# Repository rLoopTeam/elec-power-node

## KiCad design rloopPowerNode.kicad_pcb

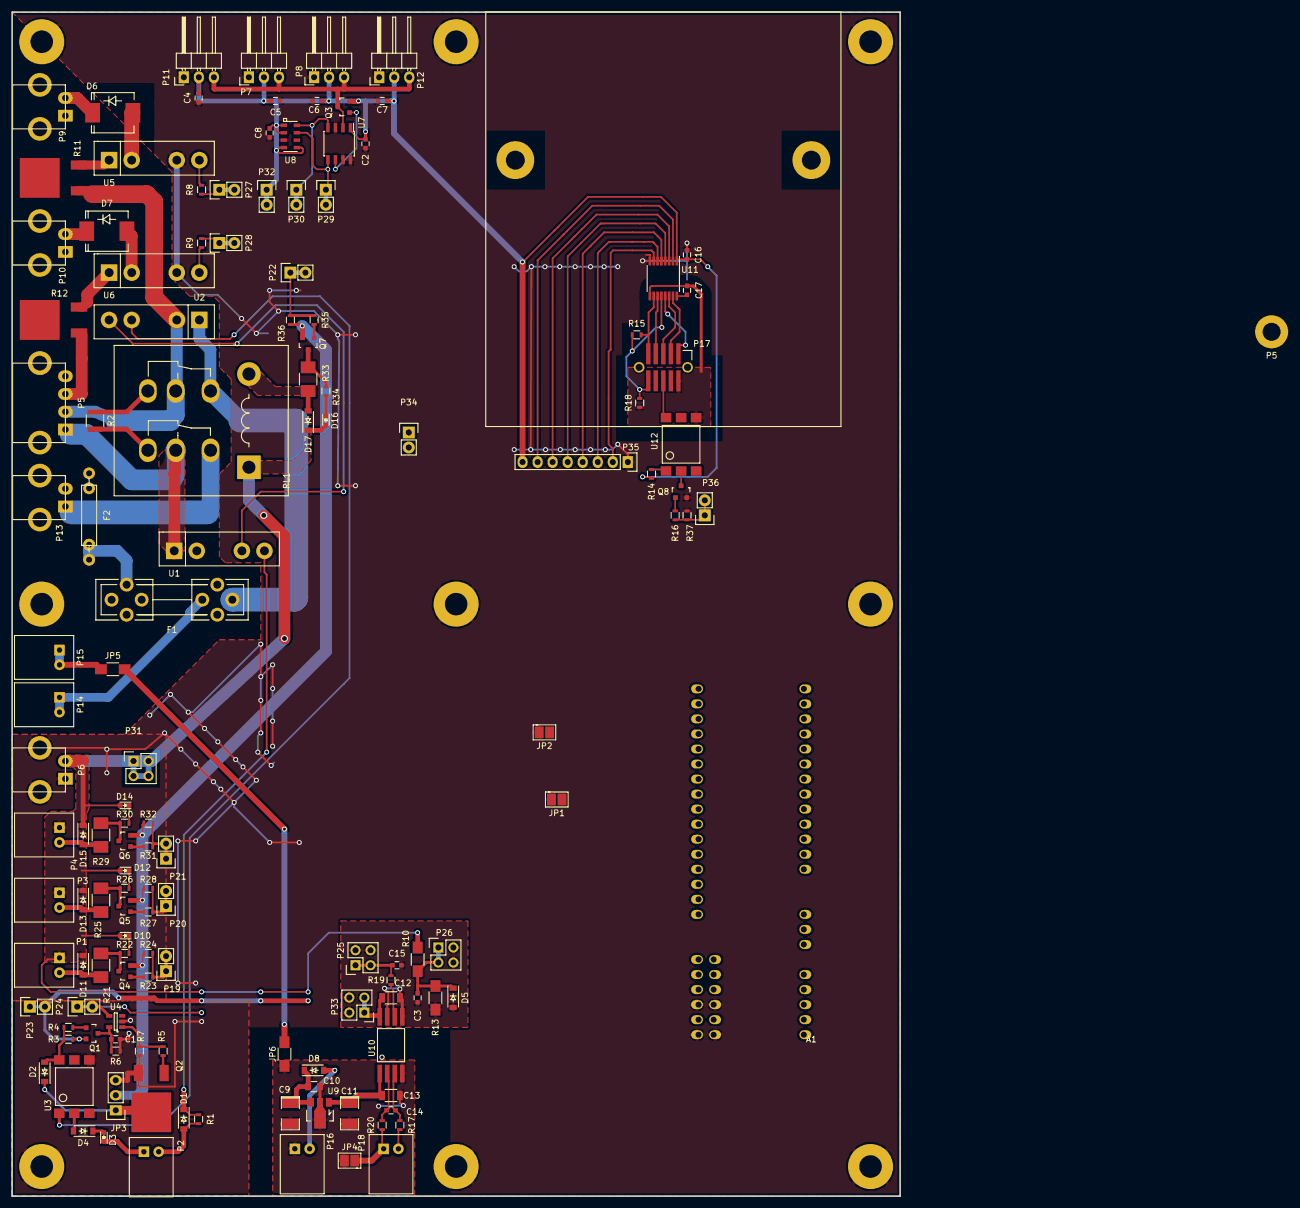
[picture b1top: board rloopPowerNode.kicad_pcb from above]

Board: 4 copper layers, 150.0 x 200.0 mm, 138 parts (0 on the bottom side), 96 nets.

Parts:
A1: NODE_CORE_CONNECTOR; NODE-CORE
C1, C2, C3, C8, C14, C16, C17: 100n; C_0603
C4, C5, C6, C7, C15: 1u; C_0603
C9, C11: 4u7; SMD-1210_Pol
C10: 1u; C_0805
C12, C13: 100n; C_1206
D1, D4, D8, D11, D13, D15, D17: D; SOD-123
D2: D_Schottky; SOD-123
D3, D10, D12, D14, D16: LED; LED_0603
D5: ZENER +2V7; SOD-123
D6, D7: D; SMC_Standard
F1: FUSE; Fuseholder5x20_horiz_open_universal_Type-III
F2: FUSE; FUSE-MULTICHOICE
JP1, JP2, JP4: Jumper_NC_Small; SOLDERJUMPER
JP3: JUMPER3; Pin_Header_Straight_1x03
JP5, JP6: Jumper_NC_Small; R_1206_HandSoldering
P1, P2, P3, P4, P14, P15, P16: CONN_01X02; CONN-JST-XH-2-PTH-RGT
P5: CONN_01X04; CONN-TE-MICROMNL-4-PTH-MALE-RGT
P5#2: CONN_01X01; SCREWPAD-4-40
P6, P9, P10, P13: CONN_01X02; CONN-TE-MICROMNL-2-PTH-MALE-RGT
P7, P8, P11, P12: CONN_01X03; Pin_Header_Angled_1x03
P17: AMPMODU-02X05; BMS
P18: SHUNT; CONN-JST-XH-2-PTH-RGT
P19, P20, P21, P22, P23, P24, P27, P28, P29, P30, P32, P34, P36: CONN_01X02; Pin_Header_Straight_1x02
P25, P26, P31, P33: CONN_02X02; Pin_Header_Straight_2x02
P35: CONN_01X08; Pin_Header_Straight_1x08
PCB1: PCB-OUTLINE; PCBOUTLINE-POWERNODE
Q1: PMOS; SOT-23
Q2: NMOS; D-Pak_TO252AA
Q3: BSS84; SOT-23
Q4, Q5, Q6, Q7: NMOS; SOT-23
Q8: Q_NMOS; SOT-23
R1: ?; R_0603
R2: 1K; R_1210
R3, R7, R15, R18, R24, R28, R32, R36, R37: 100K; R_0603
R4, R5, R14, R16: 470; R_0603
R6: 10K; R_0603
R8, R9, R19: 100; R_0603
R10: 100K; R_1206_HandSoldering
R11: 100; D-Pak-TO252AA-Resistor
R12: 10; D-Pak-TO252AA-Resistor
R13: 10K; R_1206_HandSoldering
R17, R20: 10; R_0603
R21, R25, R29, R33: R; R_1210_HandSoldering
R22, R26, R30, R34: 2K; R_0603
R23, R27, R31, R35: 470R; R_0603
RL1: Relay_DPDT; RELAY-SOCKET-K10
U1, U2, U5, U6: CPC1718
U3, U12: H11F1SM; OPTOCOUPLER-0.1in-6pin-SMD
U4: MAX6814; SOT-23-5
U7: DS2482-100; SOIC-8_3.9x4.9mm_Pitch1.27mm
U8: MS5607-02BA03; MS56xx
U9: 78L05; SOT89-3-VREG
U10: AMC1100; SOIC-8-W
U11: MAX14850; TSSOP-16_4.4x5mm_Pitch0.65mm

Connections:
+3.3V: P32.1, P32.2, P33.1, P33.3
+3V3: A1.+3V3, C2.2, C4.2, C5.2, C6.2, C7.2, C8.2, C12.1, C16.2, P7.2, P8.2, P11.2, P12.2, P35.8, Q3.2, R14.2, U7.1, U8.1, U8.2, U8.4, U8.5, U10.8, U11.1
+5V: A1.+5V, P23.1, P23.2, Q1.2, R3.1
+5V-HV: C11.1, C13.2, U9.VO, U10.1
+24V: D10.2, D11.1, D12.2, D13.1, D14.2, D15.1, D16.2, D17.1, P1.1, P3.1, P4.1, P6.2, P31.1, P31.2, P31.3, P31.4, P34.1, P34.2, R10.1, RL1.1
/Relay Driver 1/RELAY-NEG: D11.2, P1.2, R21.1
/Relay Driver 2/RELAY-NEG: D13.2, P3.2, R25.1
/Relay Driver 3/RELAY-NEG: D15.2, P4.2, R29.1
/Relay Driver 4/RELAY-NEG: D17.2, R33.1, RL1.2
BATT-ILV: P5.3, R12.1
BATT-NEG: P5.1, P5.M1, P5.M2, P9.1, P9.M1, P9.M2, P10.1, P10.M1, P10.M2, RL1.5, U1.1
BATT-POS: P5.2, R11.1, RL1.8, U2.2
BMS-CS: A1.T10, P35.3, U11.6
BMS-CS-HI: P17.7, U11.11
BMS-IRQ: A1.T33, P35.2, U11.7
BMS-IRQ-HI: P17.9, R15.2, U11.10
BMS-MISO: A1.T12, P35.5, U11.4
BMS-MISO-HI: P17.1, U11.13
BMS-MOSI: A1.T11, P35.7, U11.2
BMS-MOSI-HI: P17.3, U11.15
BMS-PD: P36.1, P36.2, R16.1, R37.1
BMS-PWRAVAIL: A1.T32, P35.4, U11.5
BMS-PWRAVAIL-HI: P17.10, R15.1, R18.2, U11.12
BMS-SCK: A1.T13, P35.6, U11.3
BMS-SCK-HI: P17.5, U11.14
DCDC-NEG: JP5.1, P13.1, P15.1, P15.2, RL1.4, U1.2
DCDC-NEG-2: C9.2, C10.2, C11.2, C13.1, JP4.2, JP6.2, P16.1, U9.GND, U10.4
DCDC-POS: F1.1, P14.1, P14.2, RL1.7, U2.1
GLV: A1.T23, C3.1, D5.1, P26.1, P26.3, R10.2, R13.1
GND: A1.GND, C1.2, C2.1, C4.1, C5.1, C6.1, C7.1, C8.1, C16.1, JP1.1, JP2.1, JP3.3, P5#2.1, P6.1, P6.M1, P6.M2, P7.1, P8.1, P11.1, P12.1, P35.1, PCB1.1, PCB1.2, PCB1.3, PCB1.4, PCB1.5, PCB1.6, PCB1.7, PCB1.8, PCB1.9, Q2.3, Q8.2, R6.1, R7.2, R37.2, U3.4, U4.2, U5.3, U6.3, U7.3, U7.7, U7.8, U8.3, U11.8
GND-BMS: C17.2, P17.2, R18.1, U11.9, U12.4
GNDA: A1.AGND, C3.2, C12.2, C15.2, D5.2, P25.2, P25.4, P26.2, P26.4, P33.2, P33.4, R13.2, U10.5, U10.7
HV-CURR: A1.T21, C15.1, P25.1, P25.3, R19.1
IHV-EXTERNAL: D6.1, P9.2
IHV-PRECHG: A1.T5, P27.1, P27.2, R8.2
ILV+: D8.2, P16.2
ILV-EXTERNAL: D7.1, P10.2
ILV-PRECHG: A1.T6, P28.1, P28.2, R9.2
unnamed: JP1.2, JP2.2
unnamed: C1.1, Q1.3, R6.2, U4.5
unnamed: C9.1, C10.1, D8.1, U9.VI
unnamed: C14.1, R17.2, U10.3
unnamed: C14.2, R20.2, U10.2
unnamed: C17.1, U11.16
unnamed: D1.1, R1.2, U1.4
unnamed: D1.2, P2.2, R1.1
unnamed: D2.1, JP3.1, Q2.4
unnamed: D2.2, R3.2, R4.2, U3.6
unnamed: D3.1, P2.1
unnamed: D3.2, D4.1
unnamed: D4.2, U3.2
unnamed: D6.2, U5.2
unnamed: D7.2, U6.2
unnamed: D10.1, R22.2
unnamed: D12.1, R26.2
unnamed: D14.1, R30.2
unnamed: D16.1, R34.2
unnamed: F1.2, F2.1
unnamed: F2.2, P13.2
unnamed: JP4.1, P18.1, R20.1
unnamed: JP5.2, JP6.1
unnamed: P7.3, P8.3, P11.3, P12.3, Q3.3, U7.2
unnamed: P17.6, U12.6
unnamed: P18.2, R17.1
unnamed: Q1.1, R4.1
unnamed: Q2.1, R5.1
unnamed: Q3.1, U7.6
unnamed: Q4.1, R23.2
unnamed: Q4.3, R21.2, R22.1
unnamed: Q5.1, R27.2
unnamed: Q5.3, R25.2, R26.1
unnamed: Q6.1, R31.2
unnamed: Q6.3, R29.2, R30.1
unnamed: Q7.1, R35.2
unnamed: Q7.3, R33.2, R34.1
unnamed: Q8.1, R16.2
unnamed: Q8.3, U12.2
unnamed: R2.1, RL1.6
unnamed: R2.2, RL1.3
unnamed: R5.2, R7.1, U4.1
unnamed: R8.1, U5.4
unnamed: R9.1, U6.4
unnamed: R11.2, U5.1
unnamed: R12.2, U6.1
unnamed: R14.1, U12.1
unnamed: R19.2, U10.6
unnamed: U1.3, U2.4
unnamed: U2.3, U3.1
RELAY-COMMON: JP3.2, Q4.2, Q5.2, Q6.2, Q7.2, R24.2, R28.2, R32.2, R36.2
RLY-DCDC: A1.T27, P22.1, P22.2, R35.1, R36.1
RLY-IHV-HIGH: A1.T24, P19.1, P19.2, R23.1, R24.1
RLY-IHV-LOW: A1.T25, P20.1, P20.2, R27.1, R28.1
RLY-ILV: A1.T26, P21.1, P21.2, R31.1, R32.1
SENS-SCL: P30.1, P30.2, U7.4, U8.8
SENS-SDA: P29.1, P29.2, U7.5, U8.7
WDT: A1.T28, P24.1, P24.2, U4.4

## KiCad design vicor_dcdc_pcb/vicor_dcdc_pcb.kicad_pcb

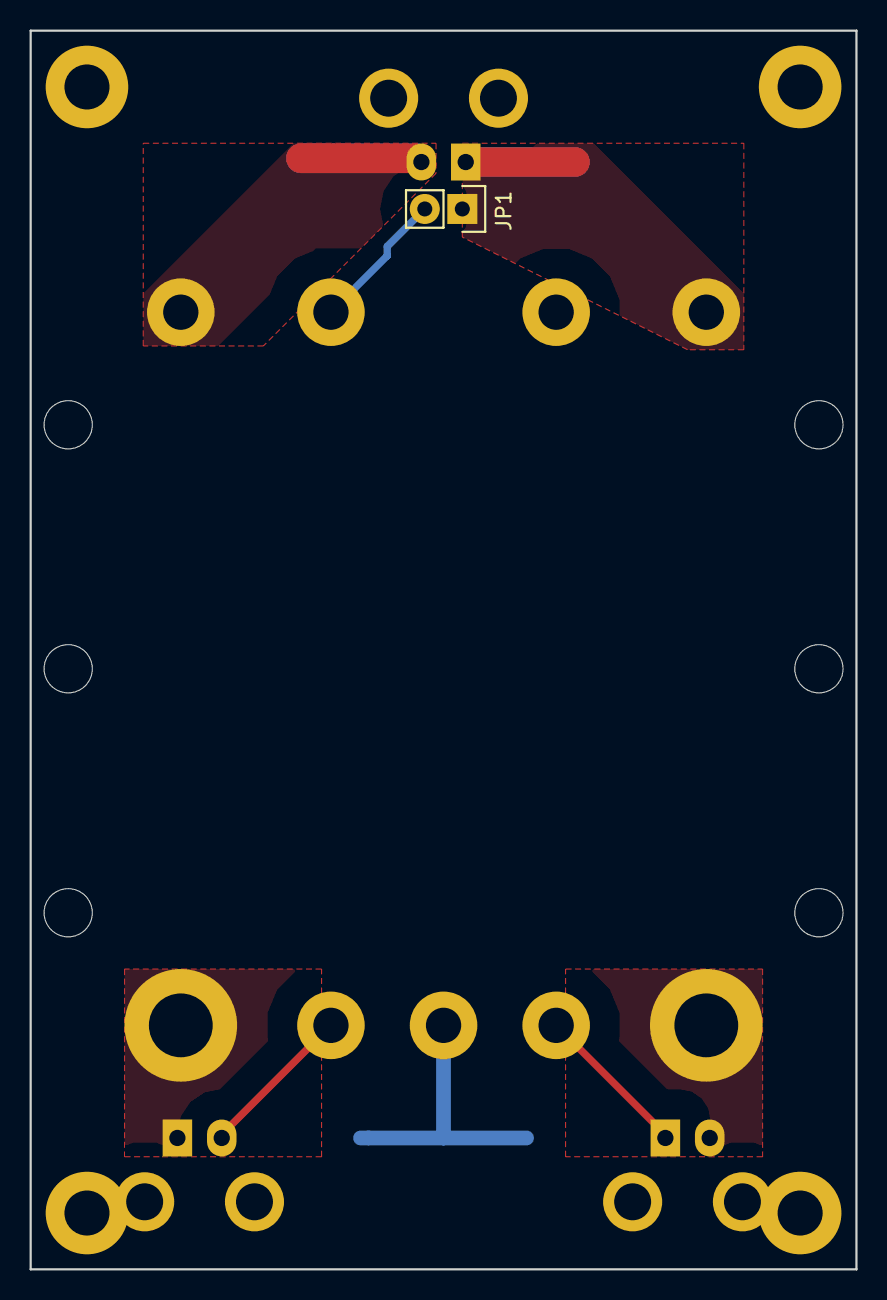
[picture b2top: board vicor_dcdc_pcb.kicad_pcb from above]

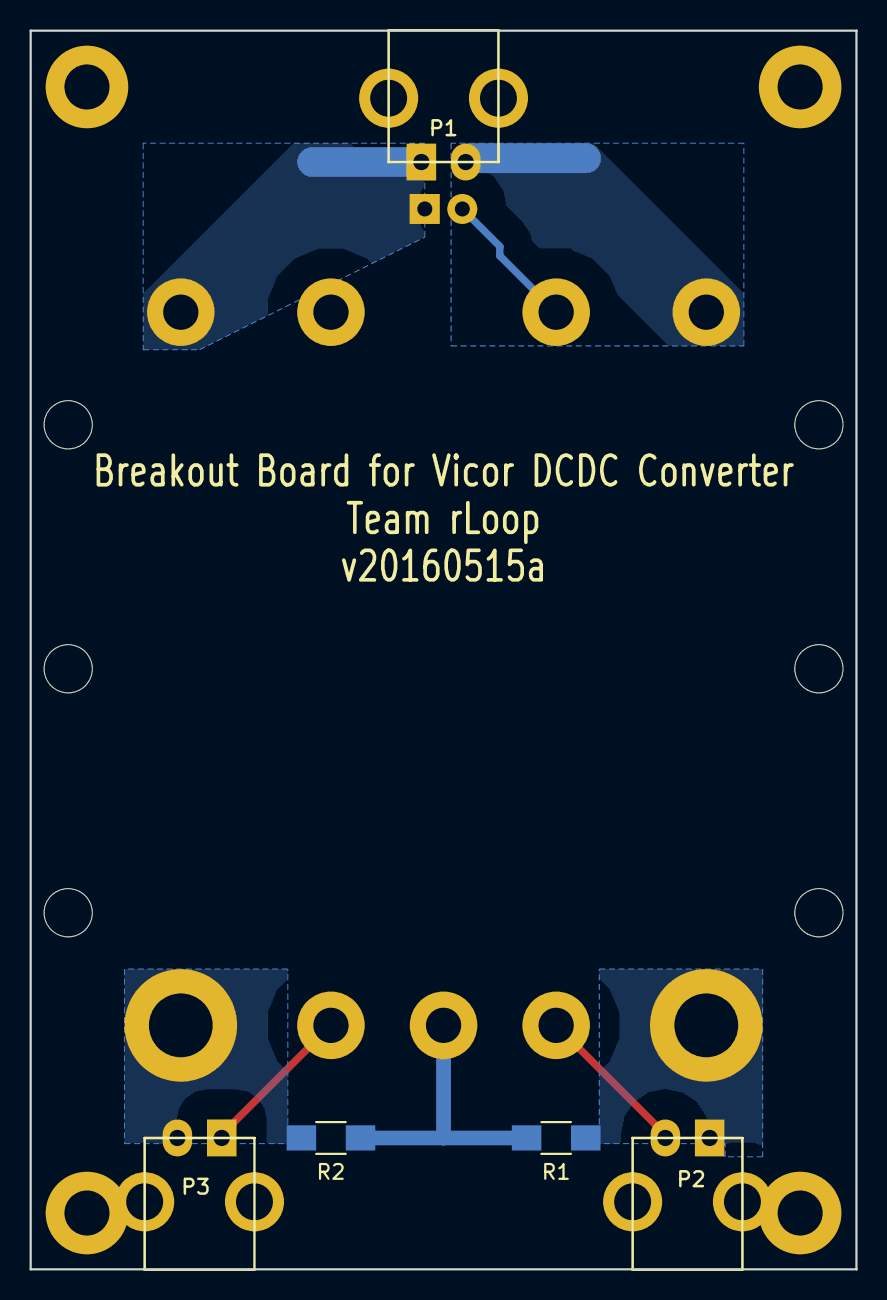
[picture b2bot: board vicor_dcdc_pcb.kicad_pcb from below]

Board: 2 copper layers, 55.9 x 83.8 mm, 7 parts (5 on the bottom side), 8 nets.

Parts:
JP1: JUMPER; Pin_Header_Straight_1x02
P1, P2, P3: CONN_01X02_2XMNT; CONN-TE-MICROMNL-2-PTH-MALE-RGT
R1, R2: R; R_1206_HandSoldering
U1: VICOR-DCDC

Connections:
unnamed: JP1.1, P1.1, U1.4
unnamed: JP1.2, U1.2
unnamed: P1.2, U1.1
unnamed: P2.1, R1.1, U1.9
unnamed: P2.2, U1.8
unnamed: P3.1, U1.6
unnamed: P3.2, R2.2, U1.5
unnamed: R1.2, R2.1, U1.7

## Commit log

2016-04-01 :space_invader: Added .gitattributes & .gitignore files
2016-04-04 Switch to DPDT relay and rearranged stuff
2016-05-03 work began
    laid out some of the top level
    started some lower level sub-circuits, such as relay drivers
2016-05-04 added some ICs, started on power, changed sheet sizes
2016-05-05 near done, TODO needs 5V sup from HV, etc
2016-05-05 added a 78L05 for the AMC1100
2016-05-07 wip showing you the latching power btn
2016-05-07 saving it in this branch, gonna toss it soon
2016-05-07 WIP but mostly done, needs connector
    latch switch changed to using photorelays
    added watchdog to relays
    added two unidirectional precharge subcircuits
    moved ILV relay to onboard
2016-05-08 added GND fault detect, conns, no pending TODOs
2016-05-08 BMS added ctrl pins, both fault outputs to MCU, ...
    added a few more comments for component selection
    directions on net labels
2016-05-08 added footprint
2016-05-09 more parts assigned
    just a check in for the meeting
2016-05-09 few connectors, cap dischg for DCDC, started layout
2016-05-10 wip some layout, added a diode to watchdog power
2016-05-11 wip layout, most subcircuits
2016-05-14 wip, bigger pads on relays, placed sensors
    HV current sensor flipped polarity
2016-05-15 added backup hookups/testpoints, a lot more routing
    subcircuits are essentially complete except the BMS mount and the node
    core, the hookups are a backup in case the node core doesn't get
    finished
2016-05-15 vicor DCDC PCB done
2016-05-16 added diode for 78L05, moved some stuff, more routing
2016-05-17 got rid of isometer connector
2016-05-17 reordered all reference designators
2016-05-17 small changes to vicor dcdc pcb
2016-05-28 laid out BMS section
